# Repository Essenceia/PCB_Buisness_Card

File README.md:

# PCB Buisness Card

Kicad files for the PCB of an NFC buisness card. 
It is powered by the loop-inductor anterna on the circuit and sends a website's address to the smartphone scanning it.

## Note
This was created with the purpose of being used at the internship fair.

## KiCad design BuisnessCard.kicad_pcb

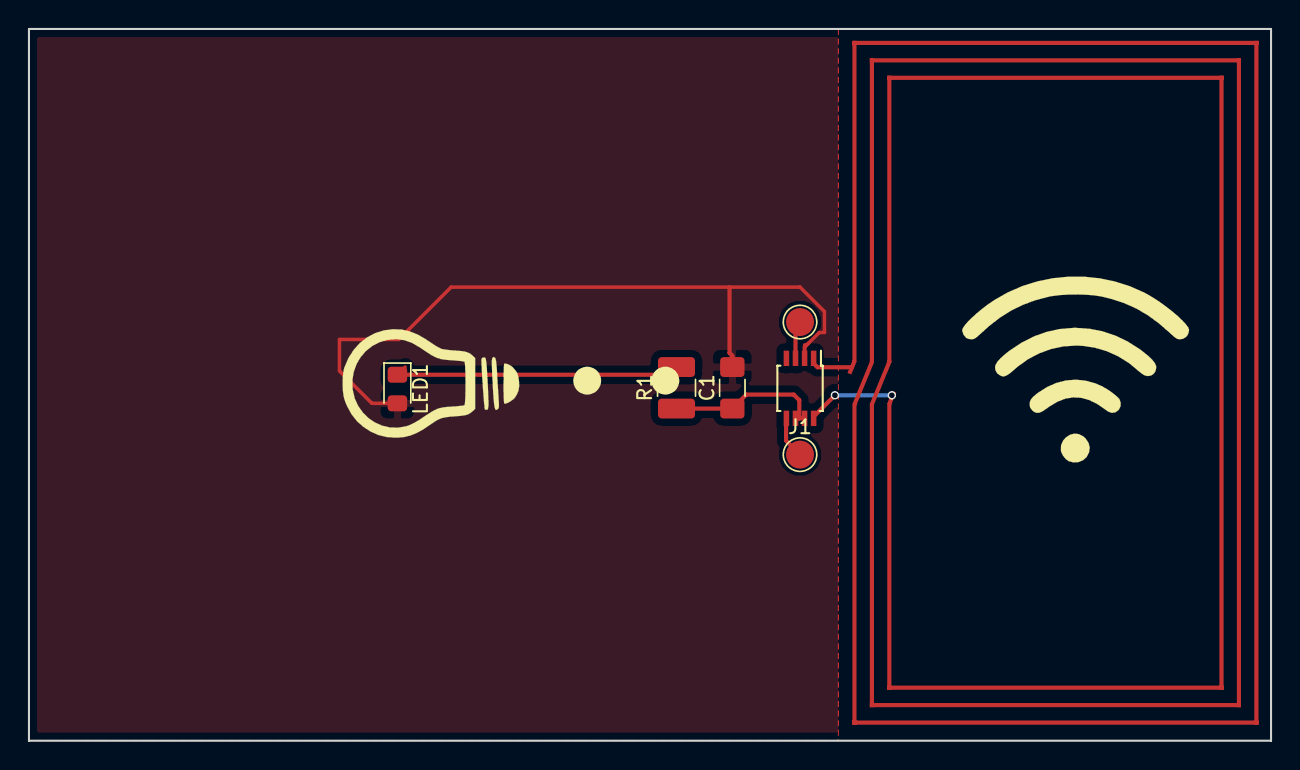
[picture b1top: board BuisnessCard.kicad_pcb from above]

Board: 2 copper layers, 89.0 x 51.0 mm, 10 parts (1 on the bottom side), 7 nets.

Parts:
AE1: Antenna_Loop; RFID_BC_Antenna
C1: 220nf; C_1206_3216Metric_Pad1.42x1.75mm_HandSolder
J1, J2: Conn_01x01_Female; TestPoint_Pad_D2.0mm
J3: Bulb; bulb
J5: pcb; wireless
J6: bash; chip
LED1: LED; LED_0805_2012Metric_Pad1.15x1.40mm_HandSolder
R1: 20; R_1210_3225Metric_Pad1.42x2.65mm_HandSolder
U1: NT3H1101; TSSOP-8_3x3mm_P0.65mm

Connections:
GND: C1.2, LED1.2, U1.2
unnamed: AE1.1, U1.1
unnamed: AE1.2, U1.8
unnamed: J1.1, U1.5
unnamed: J2.1, U1.3
unnamed: LED1.1, R1.2
VCC: C1.1, R1.1, U1.6, U1.7

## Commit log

2021-07-24 Updated readme for future reference
